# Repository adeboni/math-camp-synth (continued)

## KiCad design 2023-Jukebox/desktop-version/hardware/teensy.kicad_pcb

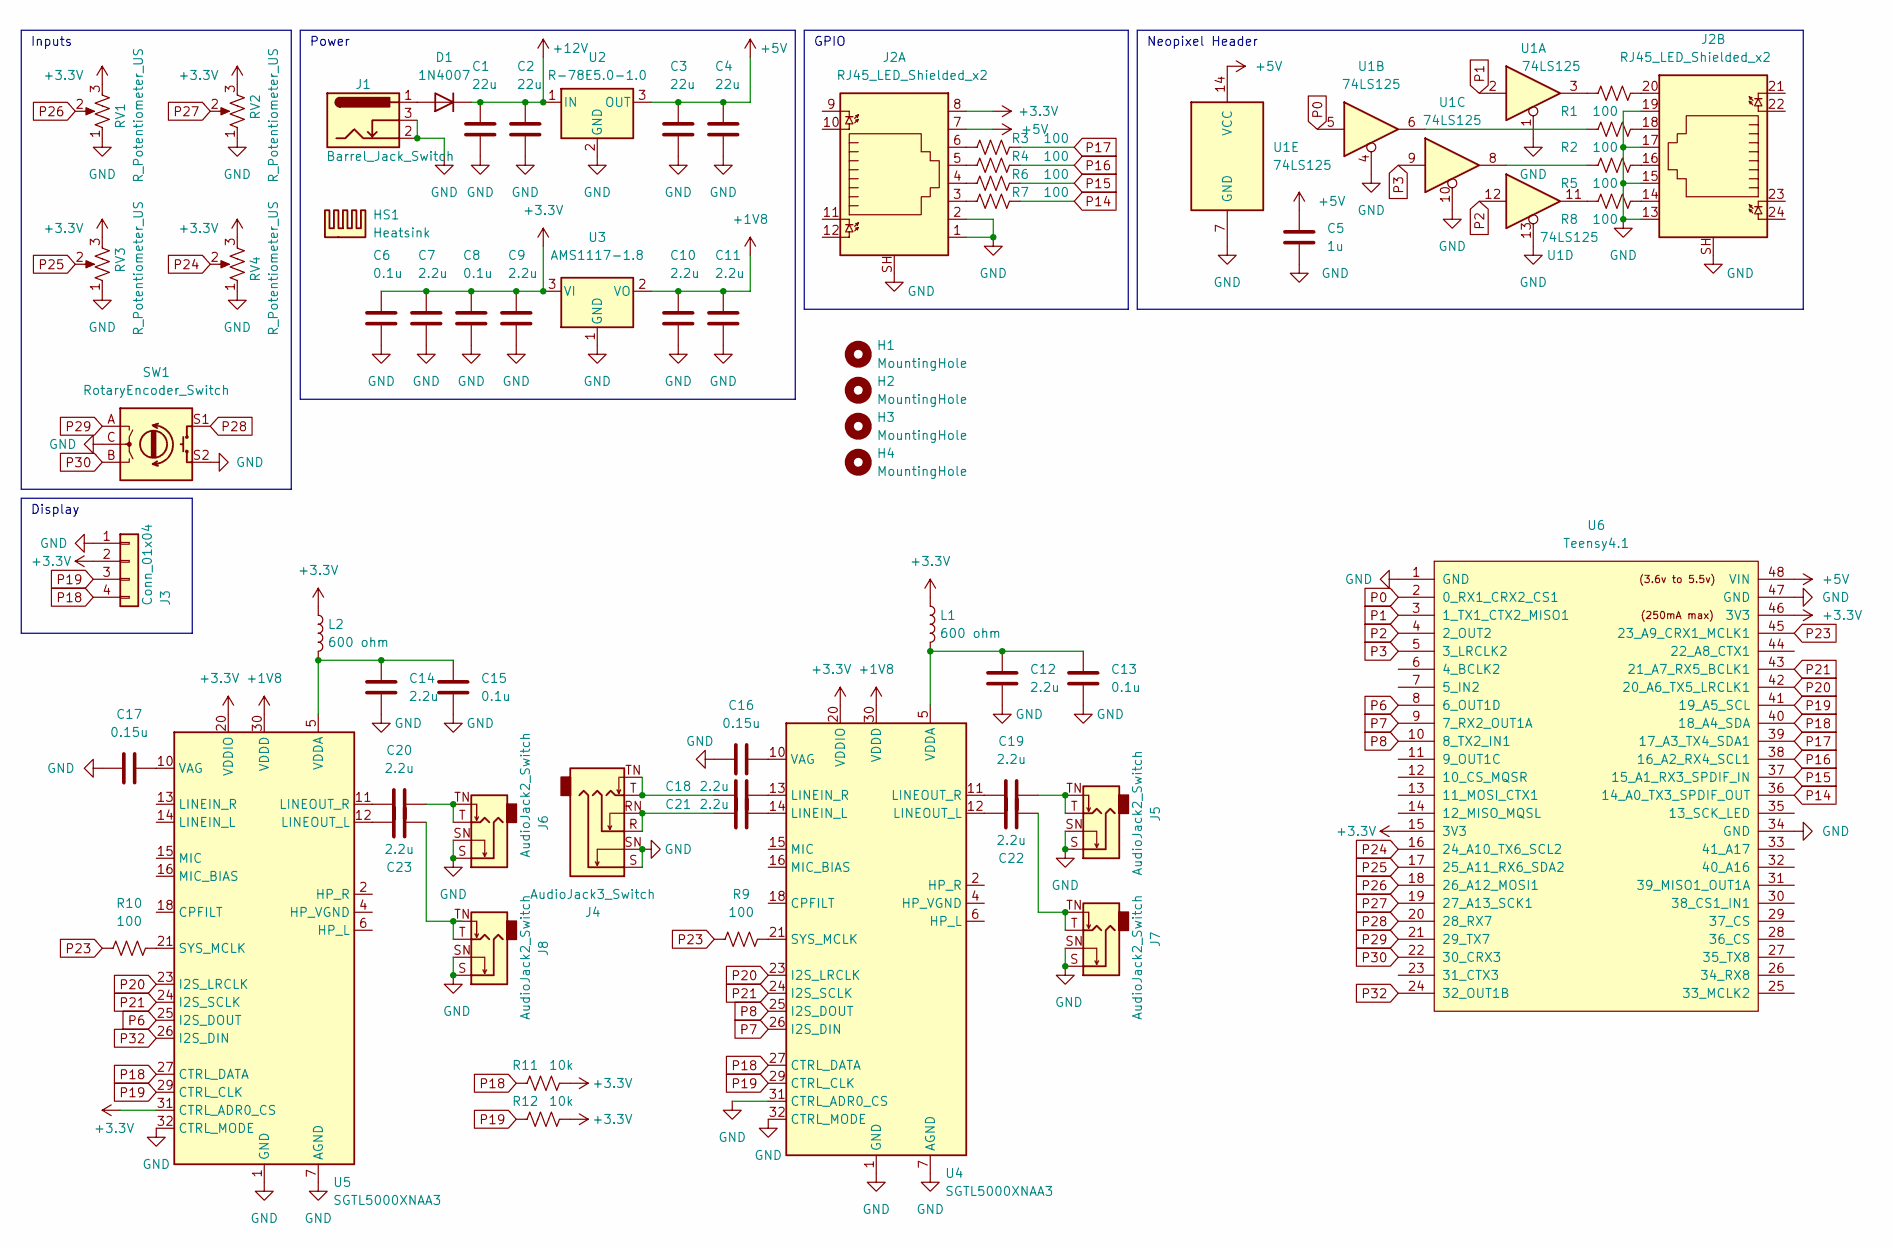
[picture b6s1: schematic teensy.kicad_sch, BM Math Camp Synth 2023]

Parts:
C1, C2, C3, C4: 22u; C_0805_2012Metric
C5: 1u; C_0603_1608Metric
C6, C8, C13, C15: 0.1u; C_0603_1608Metric
C7, C9, C10, C11, C12, C14, C18, C19, C20, C21, C22, C23: 2.2u; C_0603_1608Metric
C16, C17: 0.15u; C_0603_1608Metric
D1: 1N4007; D_DO-41_SOD81_P10.16mm_Horizontal
H1, H2, H3, H4: MountingHole; MountingHole_3.7mm
HS1: Heatsink; Heatsink_Aavid-TV5G_TO220_Horizontal
J1: Barrel_Jack_Switch; BarrelJack_Horizontal
J2: RJ45_LED_Shielded_x2; RJ45_Amphenol_RJHSE538X-02
J3: Conn_01x04; SSD1106
J4: AudioJack3_Switch; Jack_6.35mm_Neutrik_NMJ6HFD4_Horizontal
J5, J6, J7, J8: AudioJack2_Switch; Jack_6.35mm_Neutrik_NMJ6HFD4_Horizontal
L1, L2: 600 ohm; L_0603_1608Metric
R1, R2, R3, R4, R5, R6, R7, R8, R9, R10: 100; R_0603_1608Metric
R11, R12: 10k; R_0603_1608Metric
RV1, RV2, RV3, RV4: R_Potentiometer_US; Potentiometer_Alpha_RD901F-40-00D_Single_Vertical
SW1: RotaryEncoder_Switch; RotaryEncoder_Alps_EC11E-Switch_Vertical_H20mm
U1: 74LS125; SOIC-14_3.9x8.7mm_P1.27mm
U2: R-78E5.0-1.0; TO-220-3_Horizontal_TabDown
U3: AMS1117-1.8; SOT-223-3_TabPin2
U4, U5: SGTL5000XNAA3; QFN-32-1EP_5x5mm_P0.5mm_EP3.6x3.6mm
U6: Teensy4.1; Teensy41

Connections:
+1V8: C10.1, C11.1, U3.2 (VO), U4.30 (VDDD), U5.30 (VDDD)
+3V3: C6.1, C7.1, C8.1, C9.1, J2.8, J3.2, L1.1, L2.1, R11.2, R12.2, RV1.3, RV2.3, RV3.3, RV4.3, U3.3 (VI), U4.20 (VDDIO), U5.20 (VDDIO), U5.31 (CTRL_ADR0_CS), U6.15 (3V3), U6.46 (3V3)
+5V: C3.1, C4.1, C5.1, J2.7, U1.14 (VCC), U2.3 (OUT), U6.48 (VIN)
+12V: C1.1, C2.1, D1.1 (K), U2.1 (IN)
GND: C1.2, C2.2, C3.2, C4.2, C5.2, C6.2, C7.2, C8.2, C9.2, C10.2, C11.2, C12.2, C13.2, C14.2, C15.2, C16.1, C17.1, J1.2, J1.3, J2.1, J2.2, J2.13, J2.15, J2.17, J2.19, J2.SH, J3.1, J4.S, J4.SN, J5.S, J5.SN, J6.S, J6.SN, J7.S, J7.SN, J8.S, J8.SN, RV1.1, RV2.1, RV3.1, RV4.1, SW1.C, SW1.S2, U1.1, U1.4, U1.7 (GND), U1.10, U1.13, U2.2 (GND), U3.1 (GND), U4.1 (GND), U4.3 (GND), U4.7 (AGND), U4.31 (CTRL_ADR0_CS), U4.32 (CTRL_MODE), U4.33 (GND), U5.1 (GND), U5.3 (GND), U5.7 (AGND), U5.32 (CTRL_MODE), U5.33 (GND), U6.1 (GND), U6.34 (GND), U6.47 (GND)
unnamed: C12.1, C13.1, L1.2, U4.5 (VDDA)
unnamed: C14.1, C15.1, L2.2, U5.5 (VDDA)
unnamed: C16.2, U4.10 (VAG)
unnamed: C17.2, U5.10 (VAG)
unnamed: C18.1, J4.T, J4.TN
unnamed: C18.2, U4.13 (LINEIN_R)
unnamed: C19.1, U4.11 (LINEOUT_R)
unnamed: C19.2, J5.T, J5.TN
unnamed: C20.1, U5.11 (LINEOUT_R)
unnamed: C20.2, J6.T, J6.TN
unnamed: C21.1, J4.R, J4.RN
unnamed: C21.2, U4.14 (LINEIN_L)
unnamed: C22.1, U4.12 (LINEOUT_L)
unnamed: C22.2, J7.T, J7.TN
unnamed: C23.1, U5.12 (LINEOUT_L)
unnamed: C23.2, J8.T, J8.TN
unnamed: D1.2 (A), J1.1
unnamed: J2.3, R7.1
unnamed: J2.4, R6.1
unnamed: J2.5, R4.1
unnamed: J2.6, R3.1
unnamed: J2.14, R8.2
unnamed: J2.16, R5.2
unnamed: J2.18, R2.2
unnamed: J2.20, R1.2
unnamed: R1.1, U1.3
unnamed: R2.1, U1.6
unnamed: R5.1, U1.8
unnamed: R8.1, U1.11
unnamed: R9.2, U4.21 (SYS_MCLK)
unnamed: R10.2, U5.21 (SYS_MCLK)
P0: U1.5, U6.2 (0_RX1_CRX2_CS1)
P1: U1.2, U6.3 (1_TX1_CTX2_MISO1)
P2: U1.12, U6.4 (2_OUT2)
P3: U1.9, U6.5 (3_LRCLK2)
P6: U5.25 (I2S_DOUT), U6.8 (6_OUT1D)
P7: U4.26 (I2S_DIN), U6.9 (7_RX2_OUT1A)
P8: U4.25 (I2S_DOUT), U6.10 (8_TX2_IN1)
P14: R7.2, U6.36 (14_A0_TX3_SPDIF_OUT)
P15: R6.2, U6.37 (15_A1_RX3_SPDIF_IN)
P16: R4.2, U6.38 (16_A2_RX4_SCL1)
P17: R3.2, U6.39 (17_A3_TX4_SDA1)
P18: J3.4, R11.1, U4.27 (CTRL_DATA), U5.27 (CTRL_DATA), U6.40 (18_A4_SDA)
P19: J3.3, R12.1, U4.29 (CTRL_CLK), U5.29 (CTRL_CLK), U6.41 (19_A5_SCL)
P20: U4.23 (I2S_LRCLK), U5.23 (I2S_LRCLK), U6.42 (20_A6_TX5_LRCLK1)
P21: U4.24 (I2S_SCLK), U5.24 (I2S_SCLK), U6.43 (21_A7_RX5_BCLK1)
P23: R9.1, R10.1, U6.45 (23_A9_CRX1_MCLK1)
P24: RV4.2, U6.16 (24_A10_TX6_SCL2)
P25: RV3.2, U6.17 (25_A11_RX6_SDA2)
P26: RV1.2, U6.18 (26_A12_MOSI1)
P27: RV2.2, U6.19 (27_A13_SCK1)
P28: SW1.S1, U6.20 (28_RX7)
P29: SW1.A, U6.21 (29_TX7)
P30: SW1.B, U6.22 (30_CRX3)
P32: U5.26 (I2S_DIN), U6.24 (32_OUT1B)

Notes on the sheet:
GPIO
Neopixel Header
Display
Inputs
Power

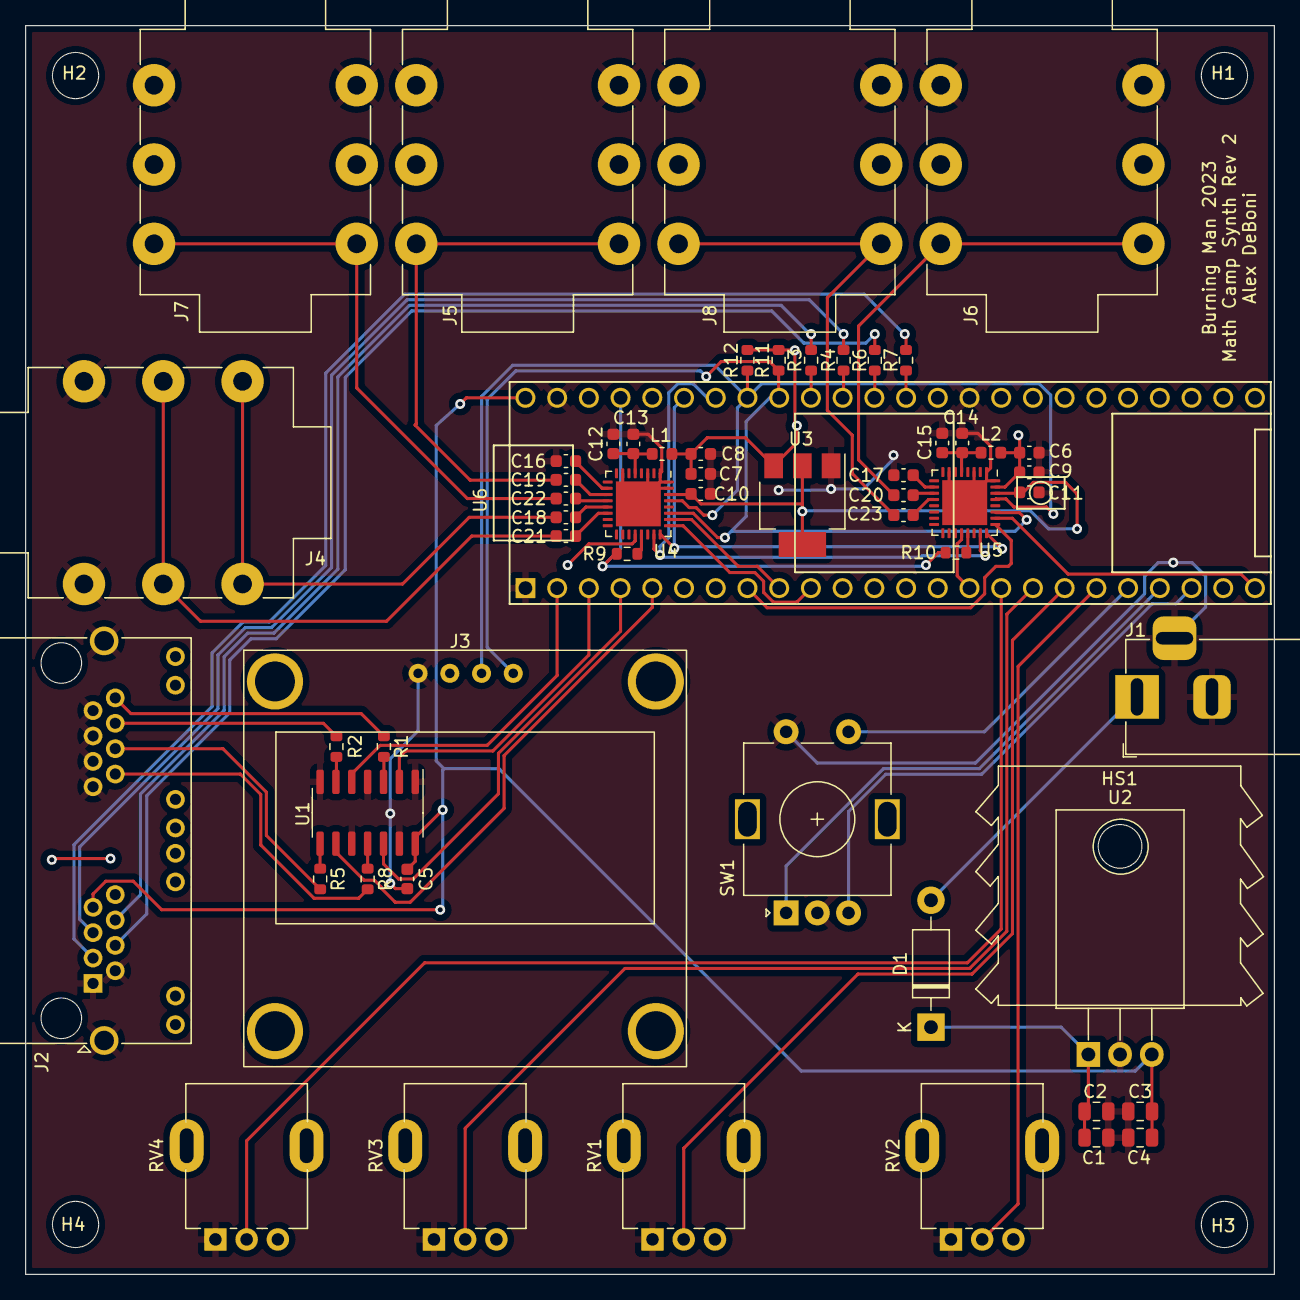
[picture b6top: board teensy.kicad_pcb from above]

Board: 2 copper layers, 100.0 x 100.0 mm, 62 parts (0 on the bottom side), 60 nets.
